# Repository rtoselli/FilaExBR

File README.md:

# FilaExBR

Código e hardware para uma filamentadora simples de baixo custo, com controle pid para a temperatura e PWM para a velocidade do motor.
O codigo está em constante desenvolvimento, acompanhe o repositório para as últimas versões.

Todo o conteúdo desse repositório está disponivel sob a licença GNU - GPL, e não me responsabilizo por qualquer dano pelo o uso impróprio dos arquivos contidos aqui.

-----

Hardware and code for a simple filament extruder control board with low cost and high power, PID and PWM for motor/temperature control. 
The code evolves fast, keep an eye for new versions. 

All files in this repository are under the GNU - GPL license, use at your own risk, i am not responsible for any harm done by the misuse of the files contained here.

# Board 

The top layer routing represent jumpers, no need for a double sided PCB!
You can see a basic functions video here : https://www.youtube.com/watch?v=0D0GXgb3E8Y

#Bill of materials
Pin Header 1x2 - 3 

Terminal block 5mm - 3

D1 - 1n4007
 
Linear Regulator 7805 - 1 

LED5MM - 2 
                                                        
Switch SPDT - 15A @ 12V - 1 

IRLB3813 N-Channel Enhancement MOSFET (HEXFET); 30V; 100A~ - 2 
                              
R1 - 220R

R2 - 220R

R3 - 47k

Trimpot 300R

ALPS rotary Encoder EC12E with switch - 1
                                                                             
ARDUINO NANO - 1

LCD Display HD44780LCD 16X02 - 1

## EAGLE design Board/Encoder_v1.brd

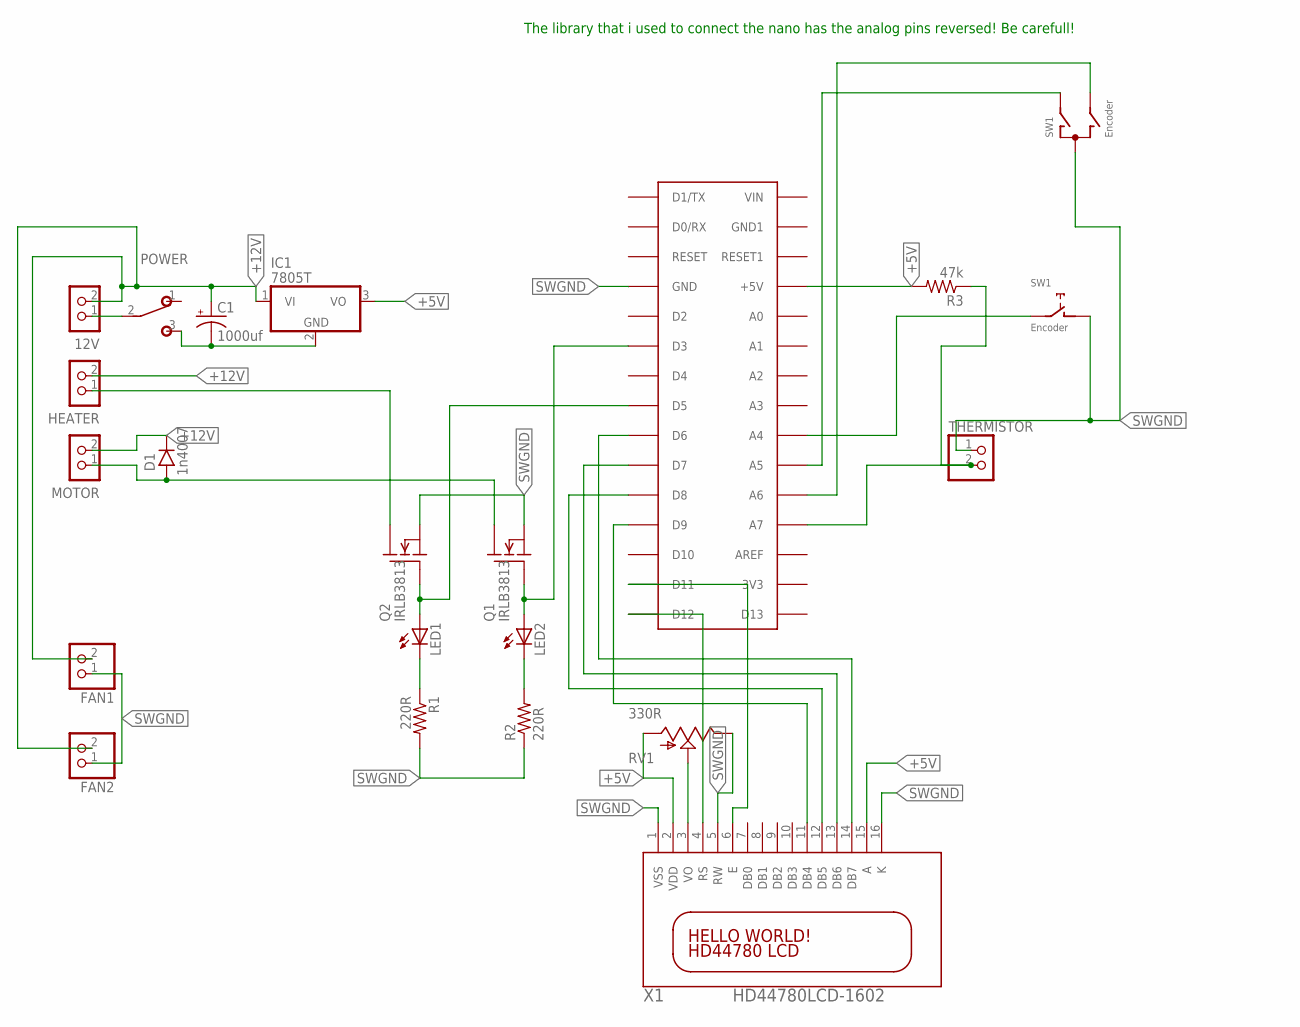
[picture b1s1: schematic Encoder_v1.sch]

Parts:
12V: CON_TERMINAL_BLOCK_02-5MM; TERMINAL_BLOCK_2P_5
A01: ARDUINO NANO; PDIP-32
C1: 1000uf; CPOL-RADIAL-1000UF-25V
D1: 1n4007; DO41-4
FAN1, FAN2: PINHD-1X2; 1X02
HEATER: CON_TERMINAL_BLOCK_02-5MM; TERMINAL_BLOCK_2P_5
IC1: 7805T; TO220H
LED1, LED2: LED5MM
MOTOR: CON_TERMINAL_BLOCK_02-5MM; TERMINAL_BLOCK_2P_5
POWER: SPDT; M9040P
Q1, Q2: IRLB3813; TO220
R1, R2: 220R; AXIAL-0.4
R3: 47k; AXIAL-0.4
RV1: 330R; TRIM_POT
SW1: Encoder; ALPS_EC12E_SW
THERMISTOR: PINHD-1X2; 1X02
X1: HD44780LCD-1602; LCD1602

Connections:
+5V: A01.+5V, IC1.3 (VO), R3.P$2 (2), RV1.3 (A), X1.2 (VDD), X1.15 (A)
+12V: 12V.2, C1.1 (+), D1.C, FAN1.2, FAN2.2, HEATER.2, IC1.1 (VI), MOTOR.2
unnamed: LED1.K (C), R1.P$1 (1)
unnamed: RV1.1 (S), X1.3 (VO)
unnamed: A01.A4, SW1.E (2)
unnamed: 12V.1, POWER.2
unnamed: A01.A6, SW1.B
unnamed: A01.A7, R3.P$1 (1), THERMISTOR.2
unnamed: A01.A5, SW1.A
unnamed: LED2.K (C), R2.P$2 (2)
unnamed: A01.D5, LED1.A, Q2.1 (G)
unnamed: A01.D6, X1.14 (DB7)
unnamed: A01.D7, X1.13 (DB6)
unnamed: D1.A, MOTOR.1, Q1.2 (D)
unnamed: A01.D3, LED2.A, Q1.1 (G)
unnamed: A01.D8, X1.12 (DB5)
unnamed: A01.D9, X1.11 (DB4)
unnamed: HEATER.1, Q2.2 (D)
unnamed: A01.D11, X1.6 (E)
unnamed: A01.D12, X1.4 (RS)
SWGND: A01.GND, C1.2 (-), FAN1.1, FAN2.1, IC1.2 (GND), POWER.3 (S), Q1.3 (S), Q2.3 (S), R1.P$2 (2), R2.P$1 (1), RV1.2 (E), SW1.C, SW1.D (1), THERMISTOR.1, X1.1 (VSS), X1.5 (RW), X1.16 (K)

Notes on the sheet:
The library that i used to connect the nano has the analog pins reversed! Be carefull!

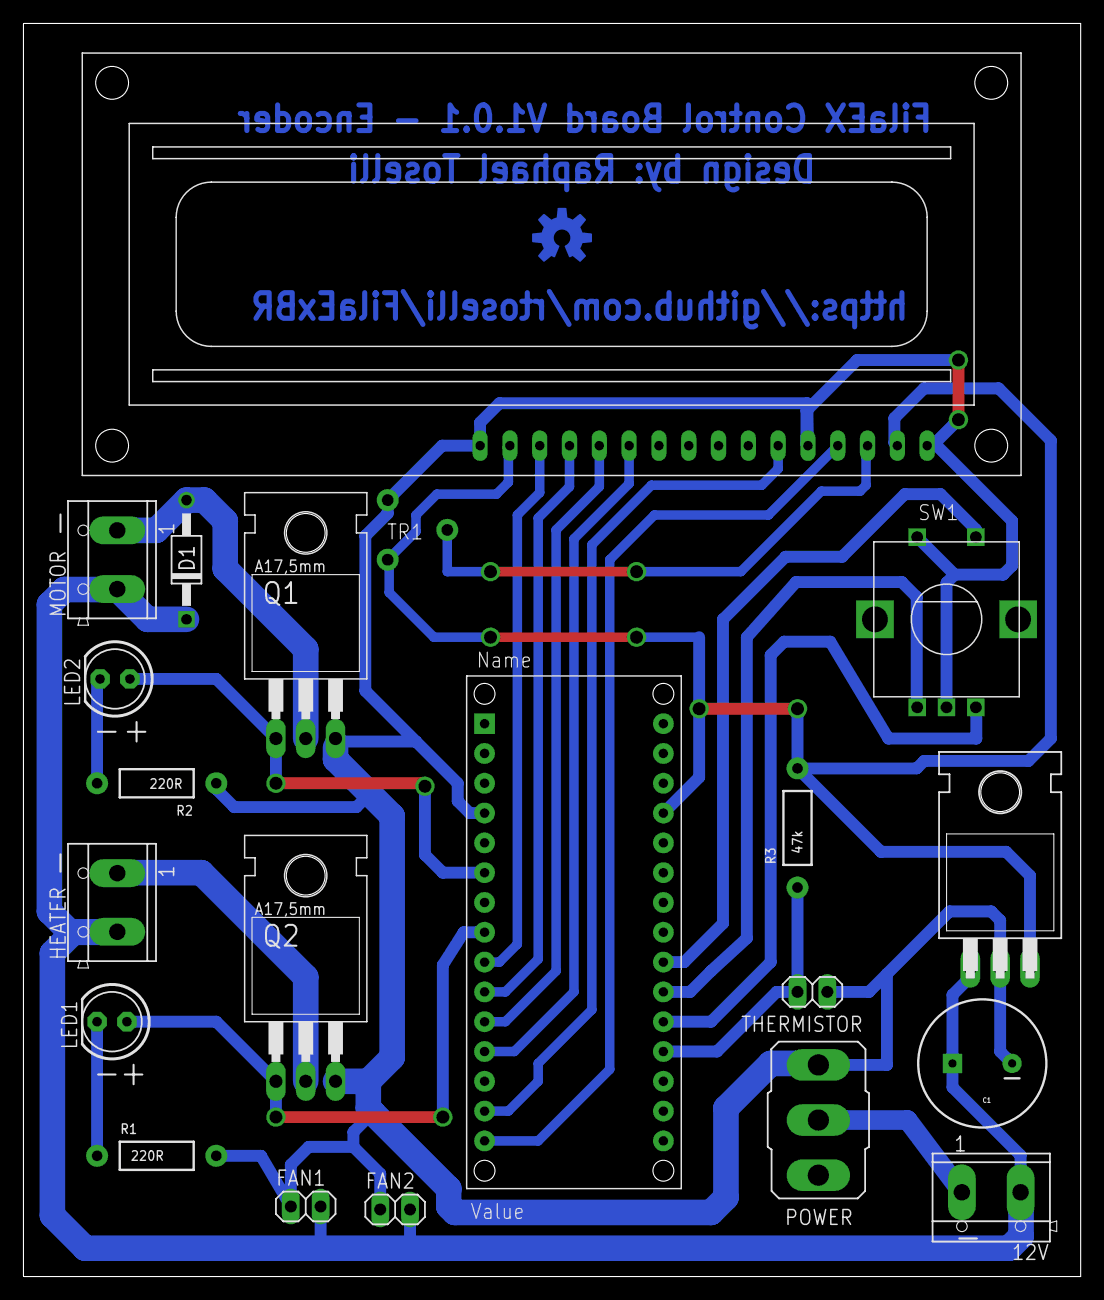
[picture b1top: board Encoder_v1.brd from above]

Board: 2 copper layers, 90.1 x 106.8 mm, 22 parts (1 on the bottom side), 21 nets.

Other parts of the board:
U$3: OSHW-LOGO-M_COPPER

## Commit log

2016-04-15 Commit Inicial
2016-04-15 Ajuste no comentario do sketch
2016-04-16 Ajuste de parametros do PID, Funçoes de debug e ajuste do nome do sketch
2016-04-16 Versão 1.0
2016-04-16 Parametros PID modificados
2016-04-18 Adição dos arquivos de layout da PCB
2016-04-18 Edição do Readme
2016-04-29 Minor Updates na placa, update do código, inicio da programação do encoder
2016-04-29 En translation
2016-04-29 Controle de menu por encoder
2016-05-03 Update board files and readme
2016-05-03 Pin adjustment on the firmware

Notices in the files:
parts and their libraries:
SparkFun-Passives: Licensing: Creative Commons ShareAlike 4.0 International - https://creativecommons.org/licenses/by-sa/4.0
